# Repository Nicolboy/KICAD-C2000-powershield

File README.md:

# KICAD-C2000-powershield

- **100W / 20V / 5A** — USB-C Power Delivery (STUSB4531QTR) feeds the
  daughter cards in daisy chain, independent from the 11-25V main input
- **5 dedicated LDOs** — isolated 3.3V reference distributed per board
  group instead of one shared regulator, removing a single point of failure
- PCB **routed 100% on 4 layers**, DRC clean

Isolation, power-supply, and interconnect shield for a TMS320 C2000 digital
power-converter controller, supervised by an ESP32-C6 for Wi-Fi, FOTA, and
an OLED status display, designed in KiCad 10.

Shield d'isolation, alimentation et interconnexion pour TMS320 C2000, conçu
sous KiCad 10.

Reprend le projet `shield` de [`KICAD-C2000-devkit`](https://github.com/Nicolboy/KICAD-C2000-devkit)
au moment où son rôle a dépassé le simple support mécanique des deux
devkits : il reçoit désormais le 11-25V externe et produit lui-même les
rails isolés (5V numérique ×2, 3,3V isolation + protection) qu'une carte
de puissance séparée portait jusque-là. D'où le changement de dépôt plutôt
qu'une extension sur place — `KICAD-C2000-devkit` reste inchangé, c'est
l'état précédent, pas un doublon à synchroniser.

Cible : une commande numérique de convertisseur de puissance isolé, pilotée
par un C2000 et supervisée par un ESP32-C6 pour le Wi-Fi, la mise à jour
FOTA et un écran OLED d'état.

---

## Architecture

| Carte | Rôle |
|---|---|
| **Shield** | Alimentation complète (11-25V→5V isolé ×2, 3,3V isolation + protection), **alimentation des cartes filles en USB-C Power Delivery** (STUSB4531QTR, 100W/20V/5A, daisy chain), support mécanique des deux devkits, adaptation de brochage, conditionnement analogique, protections, embase OLED |
| **Cartes DC/DC enfichables** | Une par fonction de puissance, portent chacune l'isolation galvanique qu'elle exige (ou aucune), raccordées au shield par les 4 nappes |
| **Devkit C2000** | MCU, deux LDO 3,3V, JTAG, bouton reset, LED, cavalier de boot |
| **Devkit ESP32** | Wi-Fi, hôte FOTA, écran OLED SPI (`ER-OLEDM032-1B`) |

Liaison shield ↔ cartes DC/DC : six nappes IDC 2 × 10 détrompées (backplane
partagé, decision #17), `3V3_ISO`/`GND` en positions 1/2 puis alternance
signal/masse stricte 1:1 sur les positions suivantes. Deux cartes
(HV, Filament) ont en plus leur propre connecteur dédié (decision #26),
leurs besoins dépassant les réserves du backplane partagé. Écran OLED :
nappe IDC 2 × 8 détrompée dédiée, alimentée avec l'ESP32. Détail complet
dans [`doc/nappes-shield.md`](doc/nappes-shield.md).

---

## Alimentation des cartes filles — USB-C Power Delivery (STUSB4531QTR)

Entrée séparée du 11-25V du shield (decision #23) : un port USB-C négocie
jusqu'à 100W (20V/5A) via un STUSB4531QTR autonome — gestion du contrat PD,
coupure (`VBUS_EN_SNK`) et décharge (`DISCH`/`VBUS_VS_DISCH`) sans eFuse
externe, un seul MOSFET P piloté directement. La puissance négociée est
transmise **en daisy chain** aux cartes filles.

Le STUSB4531 expose son bus de configuration/état (I2C : `STUSB_SCL`/
`STUSB_SDA`, alerte `STUSB_ALERT`) à l'ESP32 via un isolateur dédié
(`ISO1640BD`) — l'ESP32 peut ainsi lire la tension/le courant négociés et
réagir aux alertes sans relier directement le domaine USB-C (`GND_PRI`,
decision #27) au domaine de commande. Cette supervision rejoint son rôle
de superviseur Wi-Fi/FOTA déjà confié ailleurs dans le projet.

Détail et justification dans [`doc/decisions.md`](doc/decisions.md)
(#23, #27).

---

## Le brochage est du code

[`doc/spec-devkit.md`](doc/spec-devkit.md) fait autorité pour le connecteur
devkit — 2 × 28 pour devkit_A (hérité de `KICAD-C2000-devkit`, toujours
valable), **deux embases 2 × 24 à masse en vis-à-vis pour devkit_B**
depuis la decision #25 (`doc/decisions.md`) — les deux devkits ne sont
plus compatibles avec le même shield.
[`doc/nappes-shield.md`](doc/nappes-shield.md) décrit les quatre nappes DC/DC
et l'embase OLED. Contrairement au dépôt d'origine, **il n'y a pas de
générateur ici** — `shield.kicad_sch` est édité à la main dès le départ
(`gen_devkit.py` et consorts restent dans `KICAD-C2000-devkit`, hors sujet
pour ce dépôt).

Les schémas ne contiennent aucun fil : toute la connectivité passe par des
étiquettes globales posées exactement sur la broche concernée — convention
commune à tous les projets KiCad de l'atelier, documentée dans
[`../KICAD.md`](../KICAD.md).

---

## Concevoir avec un agent

Une part du travail est faite par un agent : lecture de datasheet, choix de
boîtier et création d'empreinte custom quand nécessaire (ex.
`lib/NCM3S1205MC.kicad_mod`), traitement par lots, étiquetage. Le placement
des composants et le routage restent manuels.

---

## Reproduire

KiCad 10 requis, `kicad-cli` dans le `PATH`.

```bash
kicad-cli sch erc --exit-code-violations shield.kicad_sch
kicad-cli pcb drc --exit-code-violations shield.kicad_pcb
```

---

## État d'avancement

Travail en cours:

- **Schéma** — dix feuilles (connecteurs devkit/ESP32/OLED, nappes DC/DC,
  alimentation, alimentation USB-C PD des cartes filles, connecteurs dédiés
  carte HV et carte Filament, quatre feuilles de chaînes de protection).
  Toutes les broches réelles portent une empreinte. L'ERC reste à quelques
  centaines de violations, de la même famille que le reste de l'atelier
  (`pin_not_connected`, `isolated_pin_label` sur des réserves non pilotées,
  `endpoint_off_grid`) — pas corrigées d'office, voir `doc/decisions.md`.
- **PCB** — **routé à 100 % sur 4 couches**. `3V3_ISO` distribué sur cinq
  régulateurs dédiés (un par groupe de nappes, décision #29 et suivantes)
  plutôt qu'un LDO unique partagé. DRC propre (quelques dizaines de
  violations résiduelles, catégorisées et justifiées — `lib_footprint_mismatch`
  attendu, `courtyards_overlap` mesuré et accepté). 14 points de test posés
  sur les rails d'alimentation, le bus I2C et la paire de référence ADC,
  étiquetés par nom de net sur `F.Silkscreen`.
- **Connecteur devkit C2000/ESP32, nappes DC/DC, embase OLED** — brochage
  figé, labels vérifiés par ERC contre les coordonnées réelles des broches.

Points encore laissés ouverts (référence exacte de certains connecteurs,
budget de courant détaillé) listés en fin de
[`doc/decisions.md`](doc/decisions.md). Ils attendent une lecture de
datasheet ou une mesure, pas une estimation.

---

## Décisions à ne pas défaire

Trente décisions documentées dans [`doc/decisions.md`](doc/decisions.md),
chacune avec sa raison et ce qui casse si on la défait. Héritées de
`KICAD-C2000-devkit` (#1 à #12) ou propres à ce dépôt (#13 à #30 : migration
de la conversion isolée sur le shield, renumérotation des nappes, embase
OLED et assignation des empreintes, connecteurs dédiés carte HV et carte
Filament, alimentation USB-C Power Delivery des cartes filles, isolation
numérique ESP32 ↔ STUSB4531, suiveur de référence ADC bufferisé).

---

## Licence

[CERN-OHL-S v2](LICENSE) — CERN Open Hardware Licence, fortement réciproque.

Tu peux étudier, modifier, fabriquer et distribuer ce matériel. En
contrepartie, si tu distribues un produit fondé dessus, ou une version
modifiée, tu dois publier les sources correspondantes sous la même licence.

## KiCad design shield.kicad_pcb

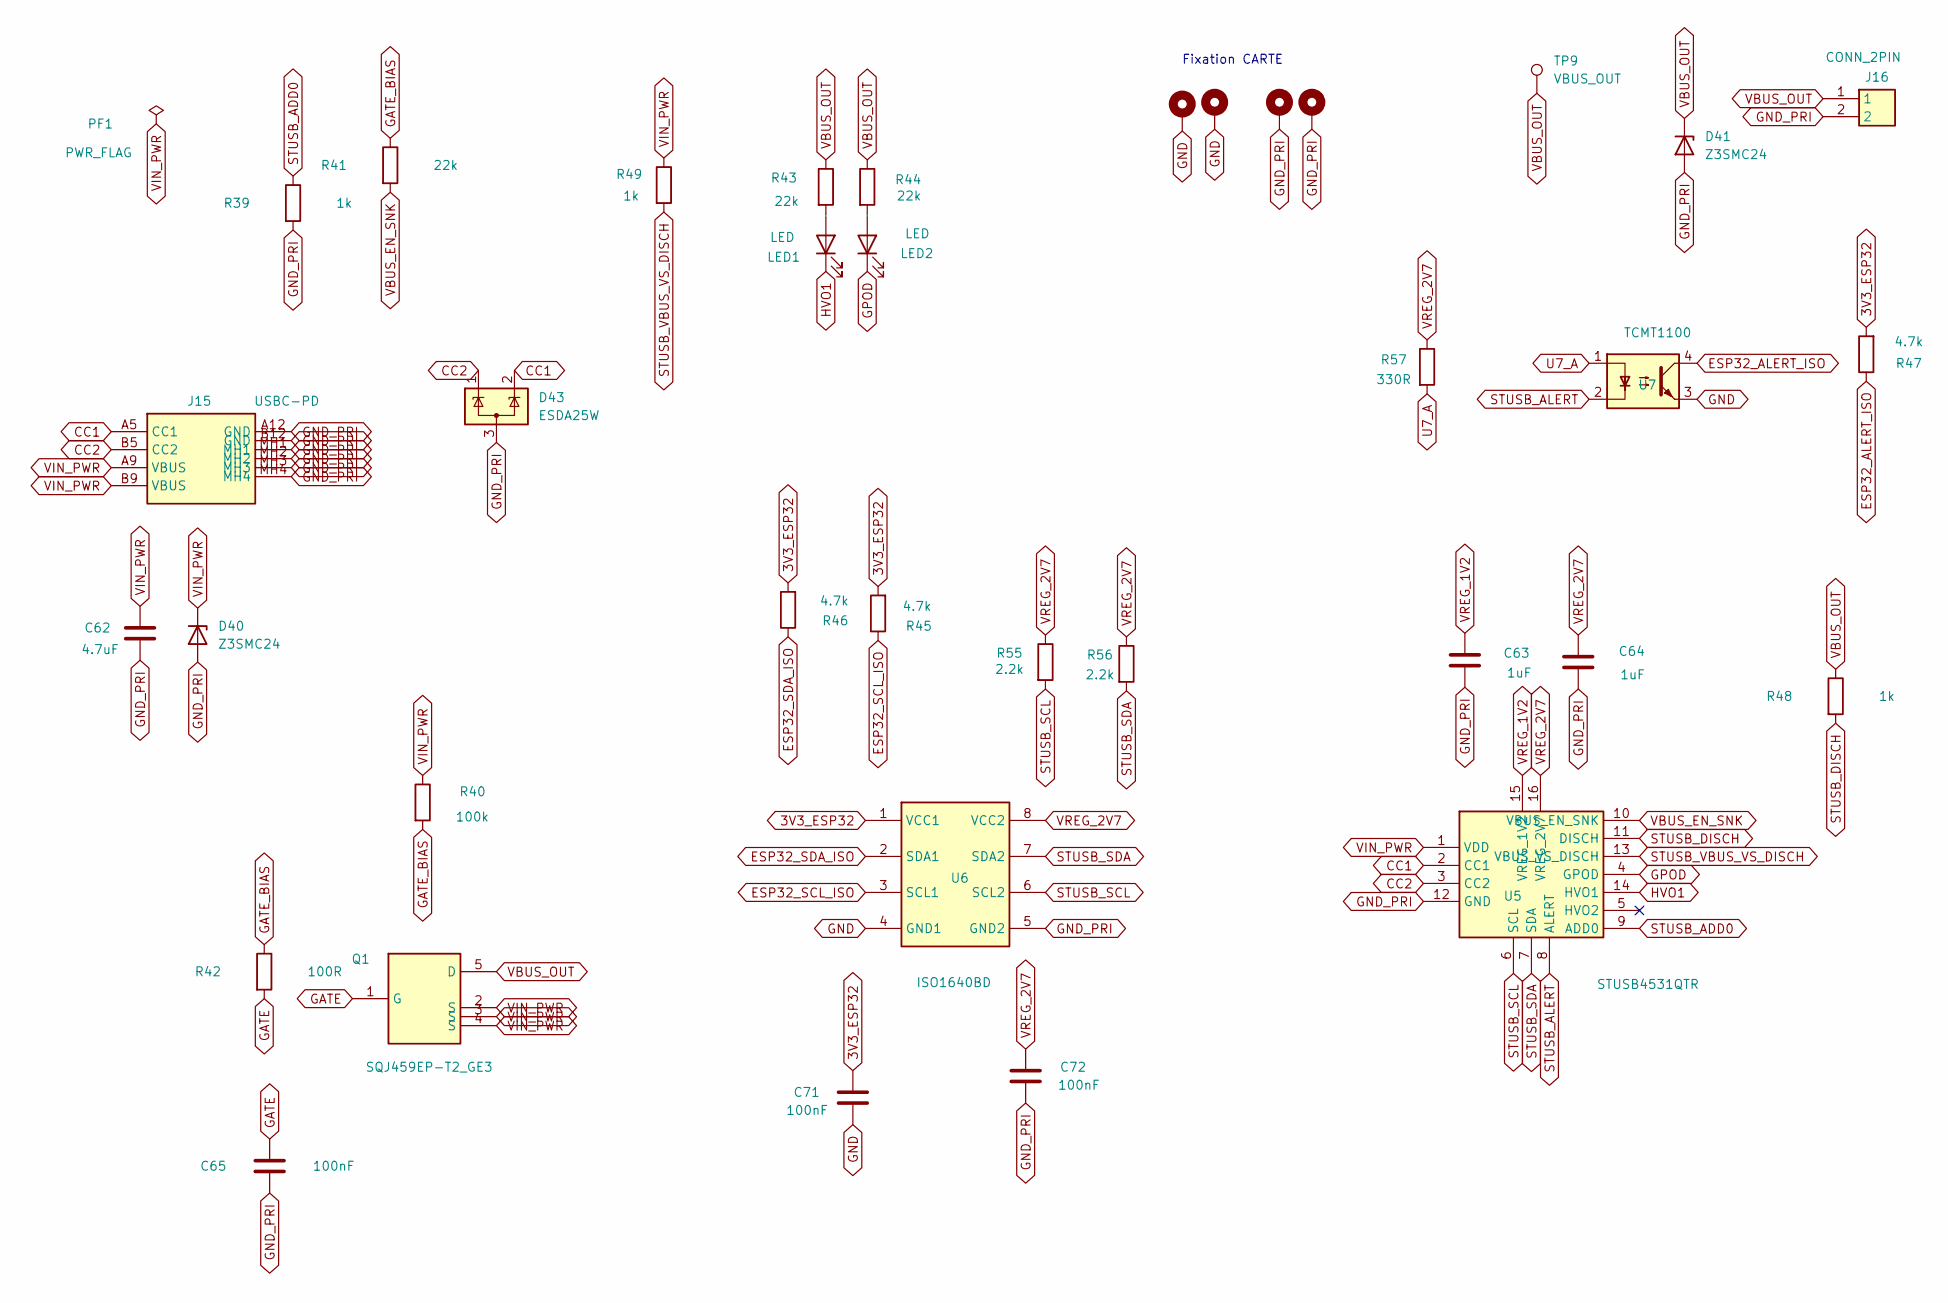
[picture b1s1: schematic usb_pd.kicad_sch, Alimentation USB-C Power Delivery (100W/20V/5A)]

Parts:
C62: 4.7uF; C_0805_2012Metric
C63, C64: 1uF; C_0805_2012Metric
C65, C71, C72: 100nF; C_0805_2012Metric
D40, D41: Z3SMC24; D_SMC
D43: ESDA25W; SOT-23-3
H1, H2, H3, H4: MountingScrew; MountingHole_3.2mm_M3_Pad_Via
J15: USBC-PD; 632722100213
J16: CONN_2PIN; PinSocket_1x02_P2.54mm_Vertical
LED1, LED2: LED; LED_D3.0mm
PF1: PWR_FLAG
Q1: SQJ459EP-T2_GE3; PowerPAK_SO-8_Single
R39, R48, R49: 1k; R_0805_2012Metric
R40: 100k; R_0805_2012Metric
R41, R43, R44: 22k; R_0805_2012Metric
R42: 100R; R_0805_2012Metric
R45, R46, R47: 4.7k; R_0805_2012Metric
R55, R56: 2.2k; R_0805_2012Metric
R57: 330R; R_0805_2012Metric
TP9: VBUS_OUT; TestPoint_Pad_D2.5mm
U5: STUSB4531QTR
U6: ISO1640BD; SOIC-8_3.9x4.9mm_P1.27mm
U7: TCMT1100; SOP-4_4.4x2.6mm_P1.27mm

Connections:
3V3_ESP32: C71.1, R45.2, R46.2, R47.2, U6.1 (VCC1); also elsewhere on the board
CC1: D43.2 (K), J15.A5 (CC1), U5.2 (CC1)
CC2: D43.1 (K), J15.B5 (CC2), U5.3 (CC2)
ESP32_ALERT_ISO: R47.1, U7.4; also elsewhere on the board
ESP32_SCL_ISO: R45.1, U6.3 (SCL1); also elsewhere on the board
ESP32_SDA_ISO: R46.1, U6.2 (SDA1); also elsewhere on the board
GATE: C65.1, Q1.1 (G), R42.2
GATE_BIAS: R40.2, R41.1, R42.1
GND: C71.2, H1.1 (1_1), H2.1 (1_1), U6.4 (GND1), U7.3; also elsewhere on the board
GND_PRI: C62.2, C63.2, C64.2, C65.2, C72.2, D40.2 (A), D41.2 (A), D43.3 (A), H3.1 (1_1), H4.1 (1_1), J15.A12 (GND), J15.B12 (GND), J15.MH1, J15.MH2, J15.MH3, J15.MH4, J16.2, R39.2, U5.12 (GND), U6.5 (GND2); also elsewhere on the board
GPOD: LED2.1 (K), U5.4 (GPOD)
HVO1: LED1.1 (K), U5.14 (HVO1)
unnamed: LED1.2 (A), R43.2
unnamed: LED2.2 (A), R44.2
STUSB_ADD0: R39.1, U5.9 (ADD0)
STUSB_ALERT: U5.8 (ALERT), U7.2
STUSB_DISCH: R48.2, U5.11 (DISCH)
STUSB_SCL: R55.2, U5.6 (SCL), U6.6 (SCL2)
STUSB_SDA: R56.2, U5.7 (SDA), U6.7 (SDA2)
STUSB_VBUS_VS_DISCH: R49.2, U5.13 (VBUS_VS_DISCH)
U7_A: R57.2, U7.1
VBUS_EN_SNK: R41.2, U5.10 (VBUS_EN_SNK)
VBUS_OUT: D41.1 (K), J16.1, Q1.5 (D), R43.1, R44.1, R48.1, TP9.1 (1_1)
VIN_PWR: C62.1, D40.1 (K), J15.A9 (VBUS), J15.B9 (VBUS), PF1.1, Q1.2 (S), Q1.3 (S), Q1.4 (S), R40.1, R49.1, U5.1 (VDD); also elsewhere on the board
VREG_1V2: C63.1, U5.15 (VREG_1V2)
VREG_2V7: C64.1, C72.1, R55.1, R56.1, R57.1, U5.16 (VREG_2V7), U6.8 (VCC2)

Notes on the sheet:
Fixation CARTE

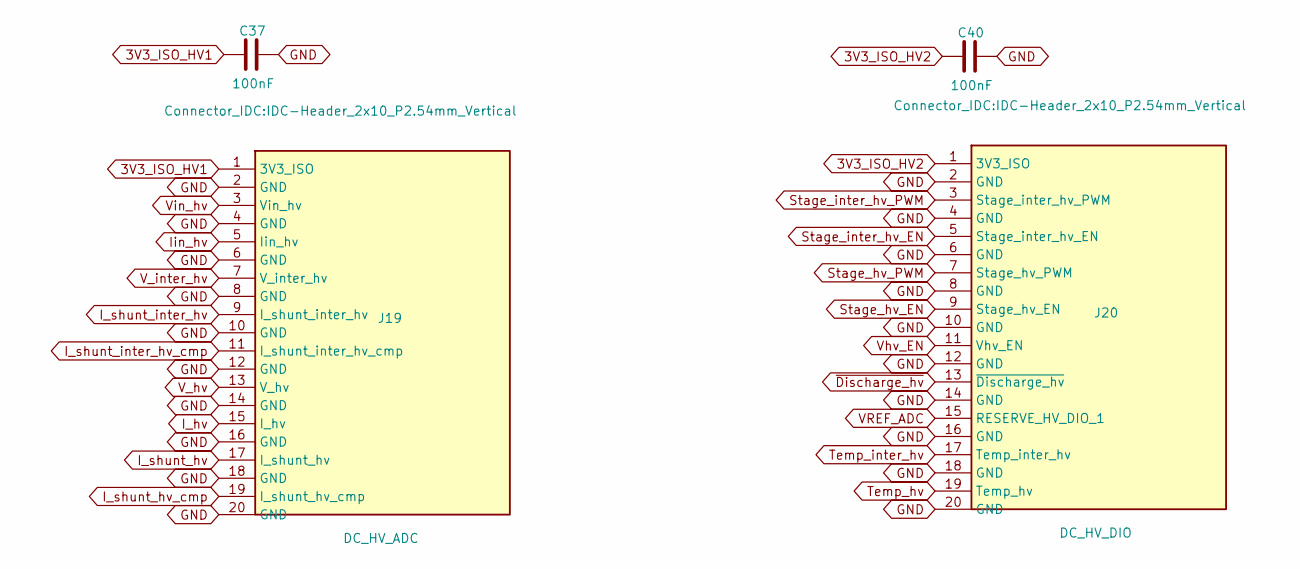
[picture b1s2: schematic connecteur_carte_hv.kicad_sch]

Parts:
C37, C40: 100nF; C_0805_2012Metric
J19: DC_HV_ADC; IDC-Header_2x10_P2.54mm_Vertical
J20: DC_HV_DIO; IDC-Header_2x10_P2.54mm_Vertical

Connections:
3V3_ISO_HV1: C37.1, J19.1 (3V3_ISO); also elsewhere on the board
3V3_ISO_HV2: C40.1, J20.1 (3V3_ISO); also elsewhere on the board
GND: C37.2, C40.2, J19.2 (GND), J19.4 (GND), J19.6 (GND), J19.8 (GND), J19.10 (GND), J19.12 (GND), J19.14 (GND), J19.16 (GND), J19.18 (GND), J19.20 (GND), J20.2 (GND), J20.4 (GND), J20.6 (GND), J20.8 (GND), J20.10 (GND), J20.12 (GND), J20.14 (GND), J20.16 (GND), J20.18 (GND), J20.20 (GND); also elsewhere on the board
I_hv: J19.15 (I_hv); also elsewhere on the board
I_shunt_hv: J19.17 (I_shunt_hv); also elsewhere on the board
I_shunt_hv_cmp: J19.19 (I_shunt_hv_cmp); also elsewhere on the board
I_shunt_inter_hv: J19.9 (I_shunt_inter_hv); also elsewhere on the board
I_shunt_inter_hv_cmp: J19.11 (I_shunt_inter_hv_cmp); also elsewhere on the board
Iin_hv: J19.5 (Iin_hv); also elsewhere on the board
Stage_hv_EN: J20.9 (Stage_hv_EN); also elsewhere on the board
Stage_hv_PWM: J20.7 (Stage_hv_PWM); also elsewhere on the board
Stage_inter_hv_EN: J20.5 (Stage_inter_hv_EN); also elsewhere on the board
Stage_inter_hv_PWM: J20.3 (Stage_inter_hv_PWM); also elsewhere on the board
Temp_hv: J20.19 (Temp_hv); also elsewhere on the board
Temp_inter_hv: J20.17 (Temp_inter_hv); also elsewhere on the board
VREF_ADC: J20.15 (RESERVE_HV_DIO_1); also elsewhere on the board
V_hv: J19.13 (V_hv); also elsewhere on the board
V_inter_hv: J19.7 (V_inter_hv); also elsewhere on the board
Vhv_EN: J20.11 (Vhv_EN); also elsewhere on the board
Vin_hv: J19.3 (Vin_hv); also elsewhere on the board
~Discharge_hv: J20.13 (~Discharge_hv); also elsewhere on the board

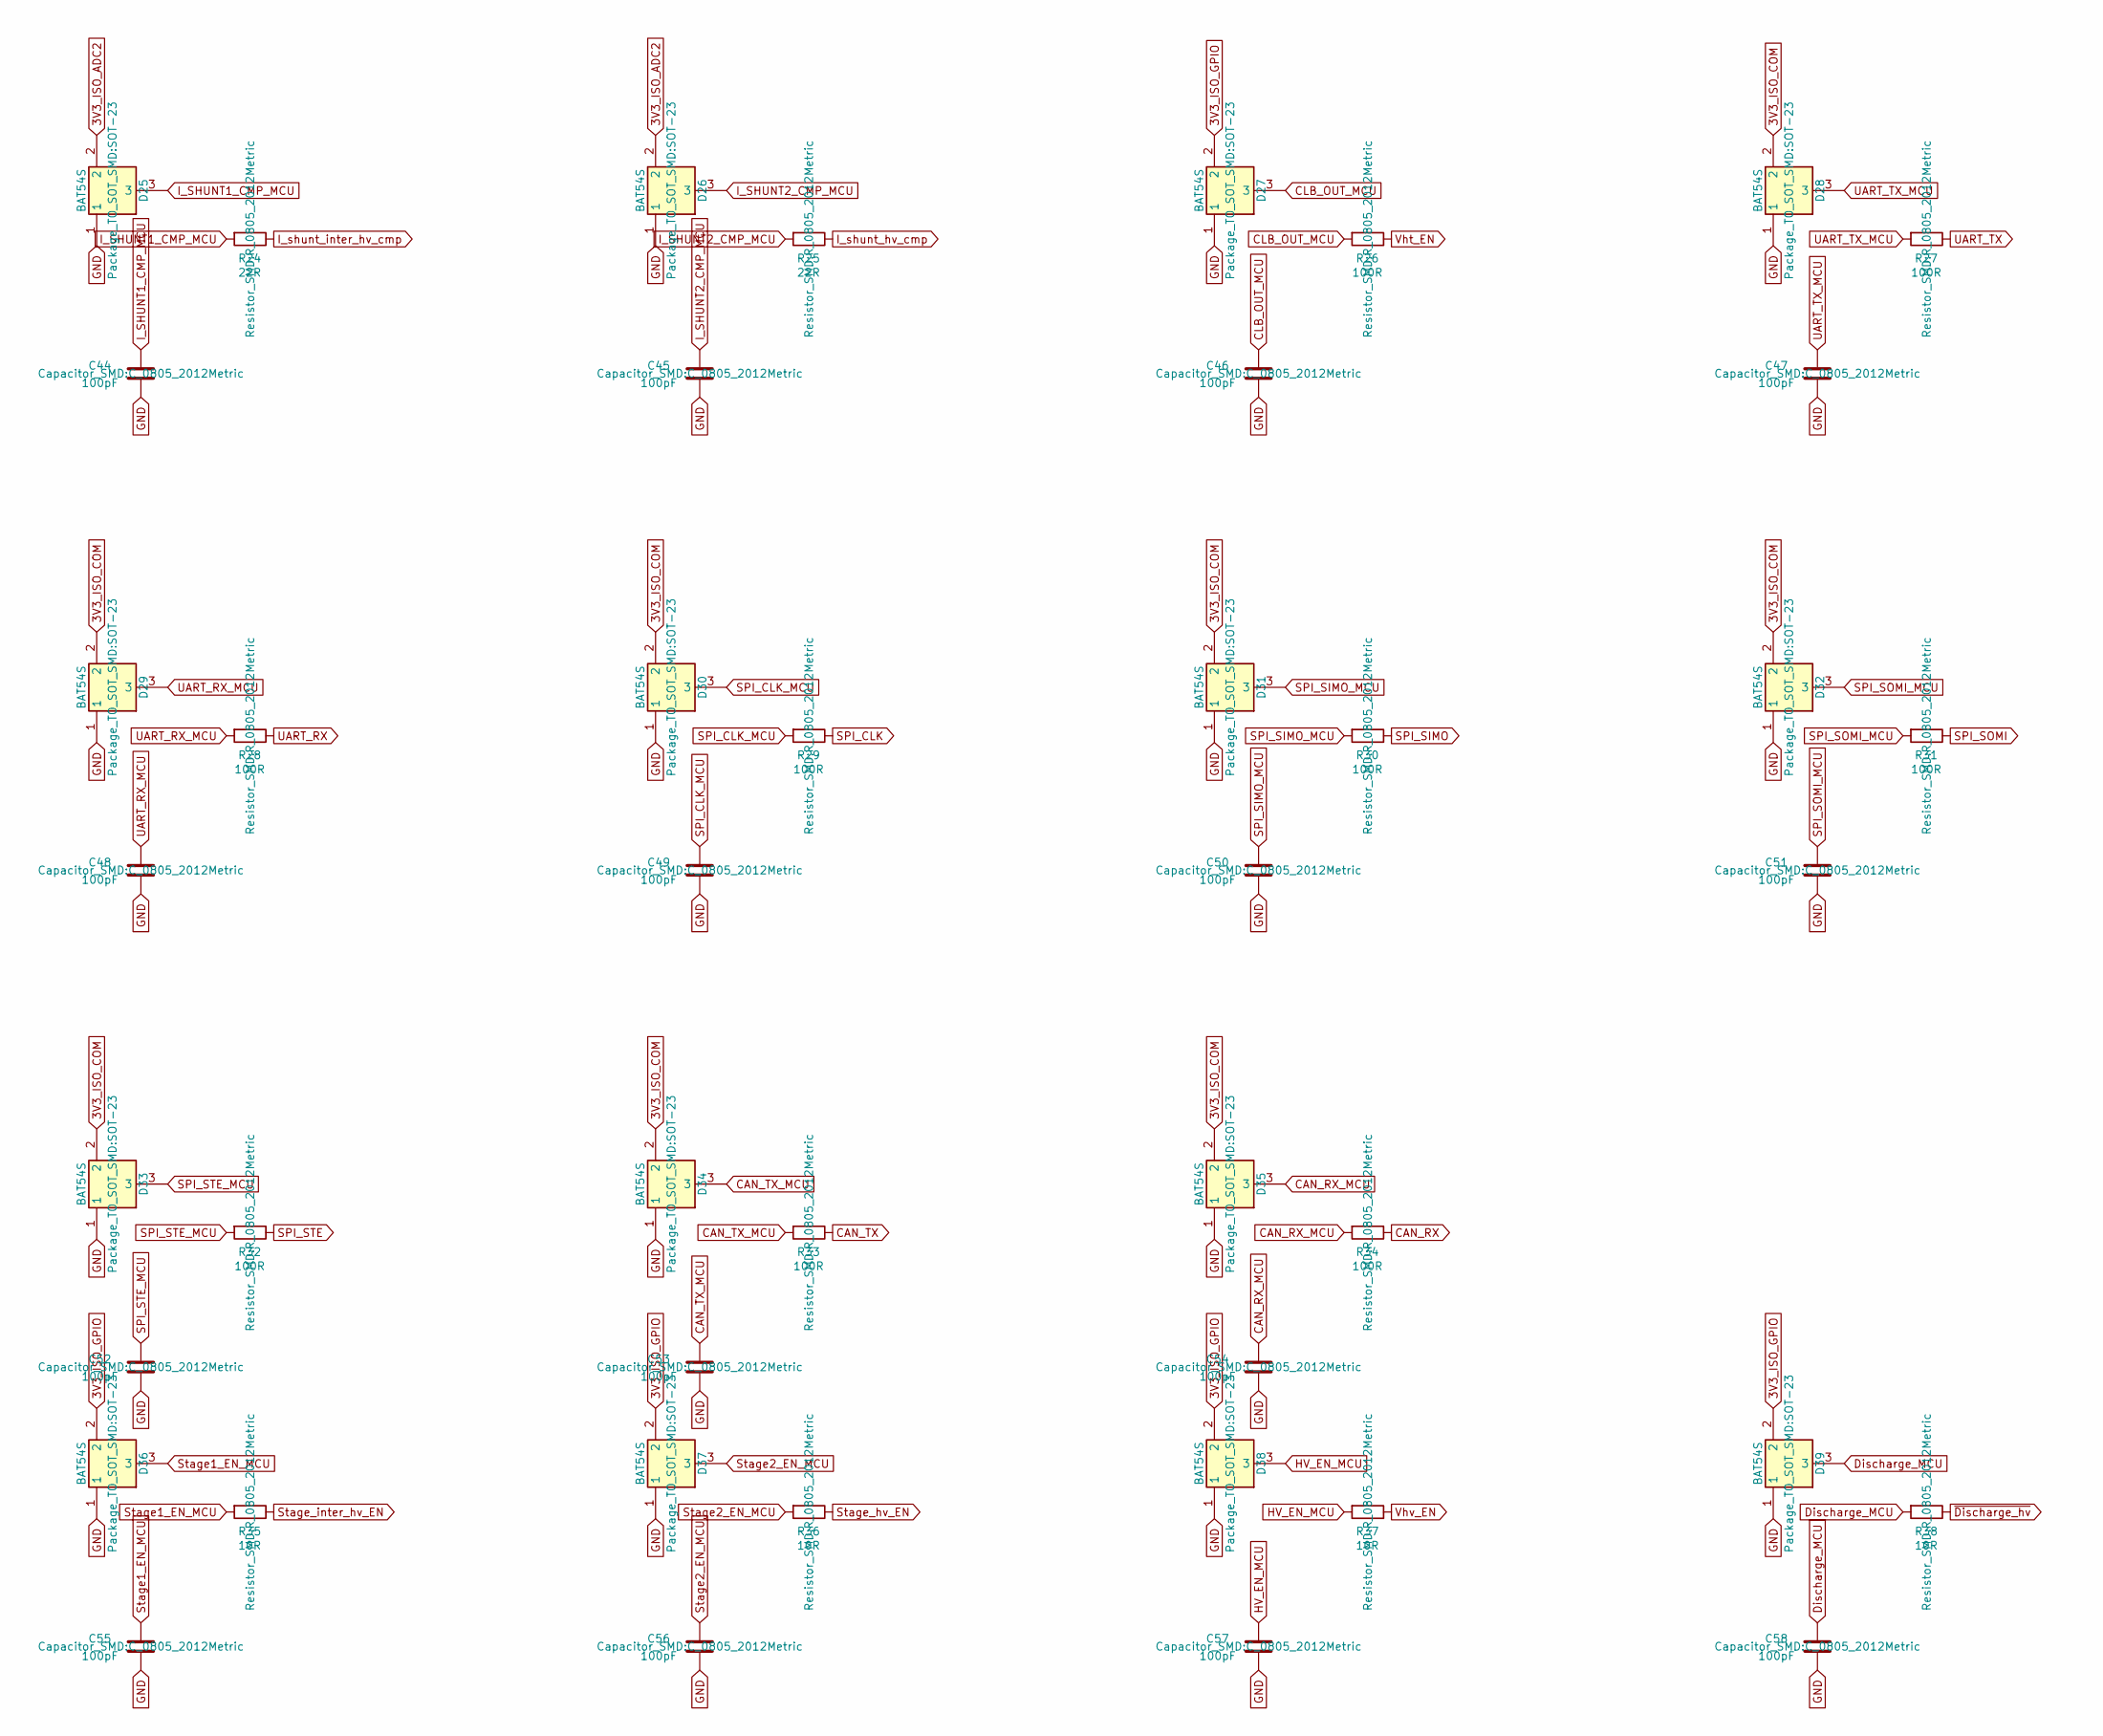
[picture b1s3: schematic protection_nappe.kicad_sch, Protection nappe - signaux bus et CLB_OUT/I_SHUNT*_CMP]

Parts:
C44, C45, C46, C47, C48, C49, C50, C51, C52, C53, C54, C55, C56, C57, C58: 100pF; C_0805_2012Metric
D25, D26, D27, D28, D29, D30, D31, D32, D33, D34, D35, D36, D37, D38, D39: BAT54S; SOT-23
R24, R25: 22R; R_0805_2012Metric
R26, R27, R28, R29, R30, R31, R32, R33, R34: 100R; R_0805_2012Metric
R35, R36, R37, R38: 10R; R_0805_2012Metric

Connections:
3V3_ISO_ADC2: D25.2, D26.2; also elsewhere on the board
3V3_ISO_COM: D28.2, D29.2, D30.2, D31.2, D32.2, D33.2, D34.2, D35.2; also elsewhere on the board
3V3_ISO_GPIO: D27.2, D36.2, D37.2, D38.2, D39.2; also elsewhere on the board
CAN_RX: R34.1; also elsewhere on the board
CAN_RX_MCU: C54.2, D35.3, R34.2; also elsewhere on the board
CAN_TX: R33.1; also elsewhere on the board
CAN_TX_MCU: C53.2, D34.3, R33.2; also elsewhere on the board
CLB_OUT_MCU: C46.2, D27.3, R26.2; also elsewhere on the board
Discharge_MCU: C58.2, D39.3, R38.2; also elsewhere on the board
GND: C44.1, C45.1, C46.1, C47.1, C48.1, C49.1, C50.1, C51.1, C52.1, C53.1, C54.1, C55.1, C56.1, C57.1, C58.1, D25.1, D26.1, D27.1, D28.1, D29.1, D30.1, D31.1, D32.1, D33.1, D34.1, D35.1, D36.1, D37.1, D38.1, D39.1; also elsewhere on the board
HV_EN_MCU: C57.2, D38.3, R37.2; also elsewhere on the board
I_SHUNT1_CMP_MCU: C44.2, D25.3, R24.2; also elsewhere on the board
I_SHUNT2_CMP_MCU: C45.2, D26.3, R25.2; also elsewhere on the board
I_shunt_hv_cmp: R25.1; also elsewhere on the board
I_shunt_inter_hv_cmp: R24.1; also elsewhere on the board
SPI_CLK: R29.1; also elsewhere on the board
SPI_CLK_MCU: C49.2, D30.3, R29.2; also elsewhere on the board
SPI_SIMO: R30.1; also elsewhere on the board
SPI_SIMO_MCU: C50.2, D31.3, R30.2; also elsewhere on the board
SPI_SOMI: R31.1; also elsewhere on the board
SPI_SOMI_MCU: C51.2, D32.3, R31.2; also elsewhere on the board
SPI_STE: R32.1; also elsewhere on the board
SPI_STE_MCU: C52.2, D33.3, R32.2; also elsewhere on the board
Stage1_EN_MCU: C55.2, D36.3, R35.2; also elsewhere on the board
Stage2_EN_MCU: C56.2, D37.3, R36.2; also elsewhere on the board
Stage_hv_EN: R36.1; also elsewhere on the board
Stage_inter_hv_EN: R35.1; also elsewhere on the board
UART_RX: R28.1; also elsewhere on the board
UART_RX_MCU: C48.2, D29.3, R28.2; also elsewhere on the board
UART_TX: R27.1; also elsewhere on the board
UART_TX_MCU: C47.2, D28.3, R27.2; also elsewhere on the board
Vht_EN: R26.1; also elsewhere on the board
Vhv_EN: R37.1; also elsewhere on the board
~Discharge_hv: R38.1; also elsewhere on the board

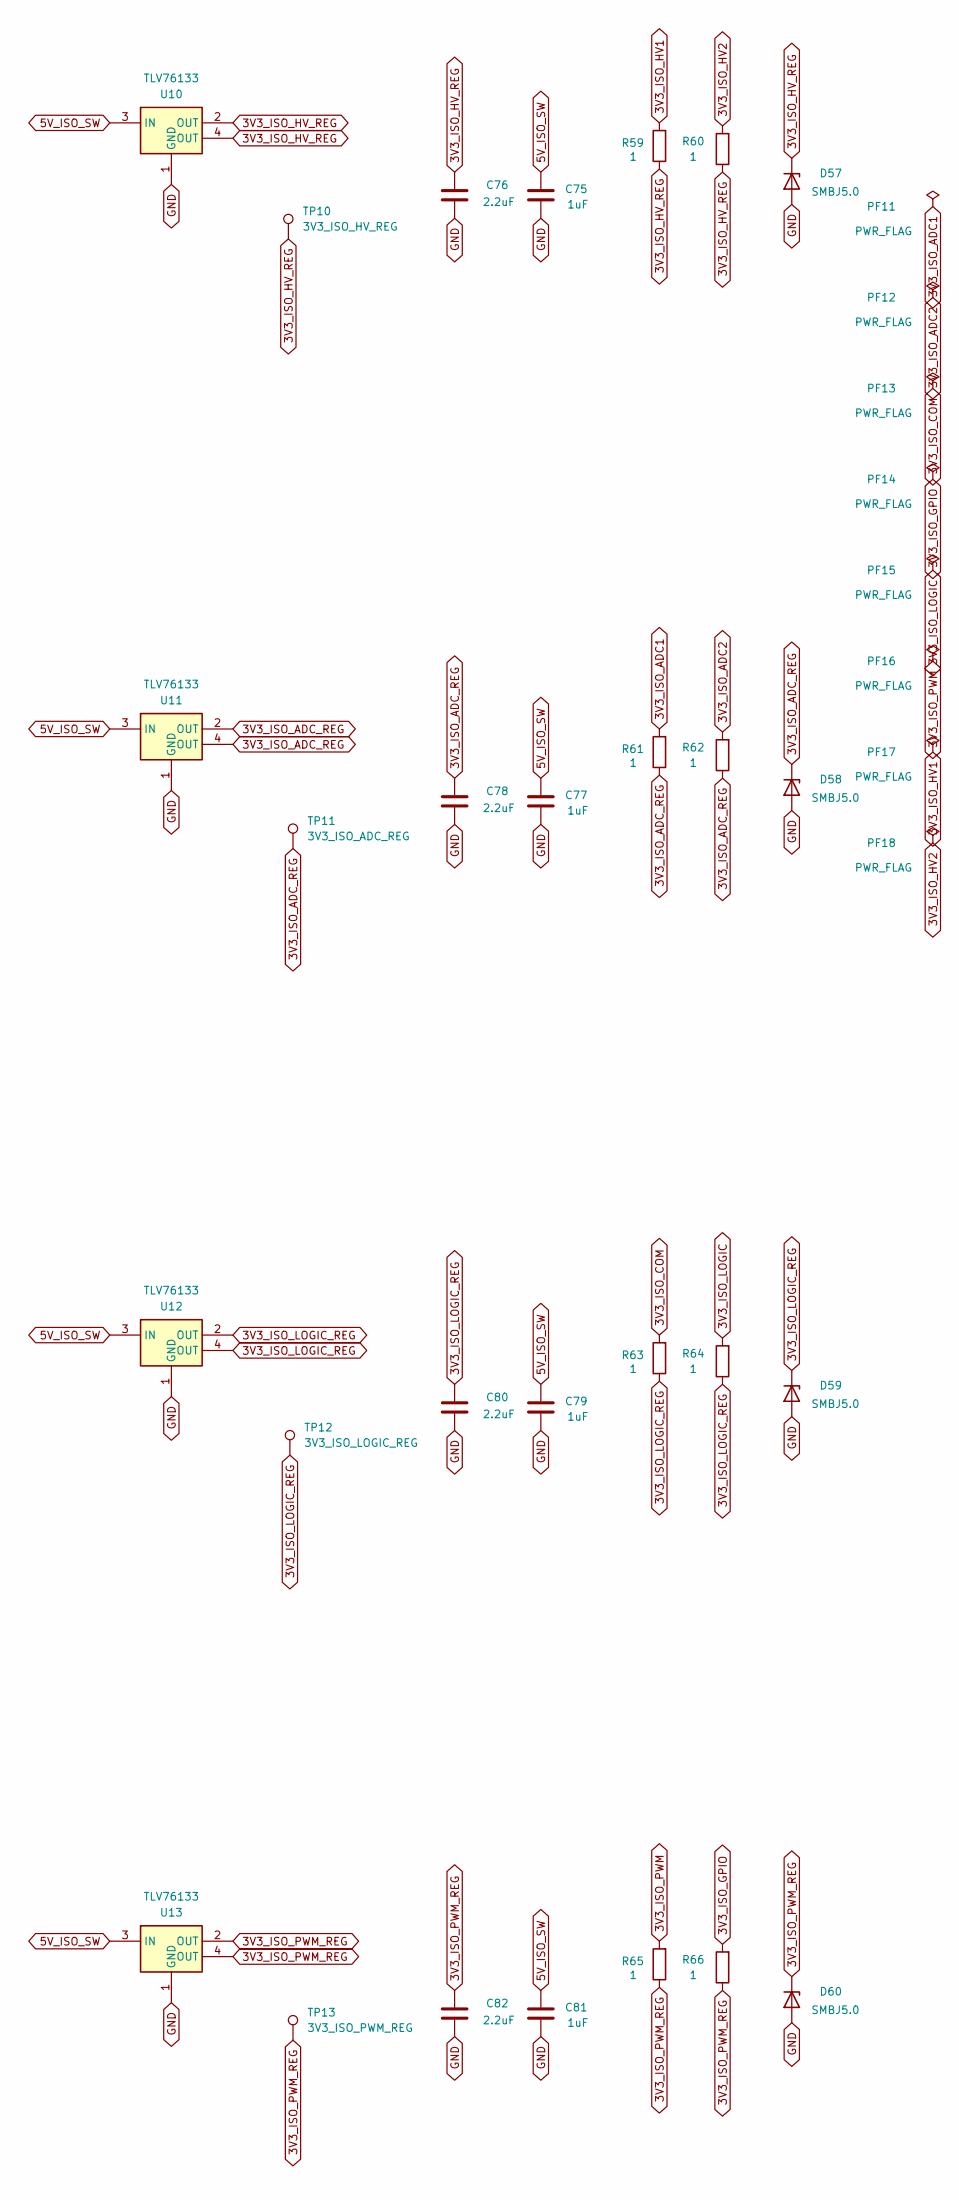
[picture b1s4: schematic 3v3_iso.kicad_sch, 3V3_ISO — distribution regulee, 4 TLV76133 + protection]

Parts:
C75, C77, C79, C81: 1uF; C_0805_2012Metric
C76, C78, C80, C82: 2.2uF; C_0805_2012Metric
D57, D58, D59, D60: SMBJ5.0; D_SMB
PF11, PF12, PF13, PF14, PF15, PF16, PF17, PF18: PWR_FLAG
R59, R60, R61, R62, R63, R64, R65, R66: 1; R_0805_2012Metric
TP10: 3V3_ISO_HV_REG; TestPoint_Pad_D2.5mm
TP11: 3V3_ISO_ADC_REG; TestPoint_Pad_D2.5mm
TP12: 3V3_ISO_LOGIC_REG; TestPoint_Pad_D2.5mm
TP13: 3V3_ISO_PWM_REG; TestPoint_Pad_D2.5mm
U10, U11, U12, U13: TLV76133; SOT-223

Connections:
3V3_ISO_ADC1: PF11.1, R61.2; also elsewhere on the board
3V3_ISO_ADC2: PF12.1, R62.2; also elsewhere on the board
3V3_ISO_ADC_REG: C78.1, D58.1 (K), R61.1, R62.1, TP11.1 (1_1), U11.2 (OUT), U11.4 (OUT)
3V3_ISO_COM: PF13.1, R63.2; also elsewhere on the board
3V3_ISO_GPIO: PF14.1, R66.2; also elsewhere on the board
3V3_ISO_HV1: PF17.1, R59.2; also elsewhere on the board
3V3_ISO_HV2: PF18.1, R60.2; also elsewhere on the board
3V3_ISO_HV_REG: C76.1, D57.1 (K), R59.1, R60.1, TP10.1 (1_1), U10.2 (OUT), U10.4 (OUT)
3V3_ISO_LOGIC: PF15.1, R64.2; also elsewhere on the board
3V3_ISO_LOGIC_REG: C80.1, D59.1 (K), R63.1, R64.1, TP12.1 (1_1), U12.2 (OUT), U12.4 (OUT)
3V3_ISO_PWM: PF16.1, R65.2; also elsewhere on the board
3V3_ISO_PWM_REG: C82.1, D60.1 (K), R65.1, R66.1, TP13.1 (1_1), U13.2 (OUT), U13.4 (OUT)
5V_ISO_SW: C75.1, C77.1, C79.1, C81.1, U10.3 (IN), U11.3 (IN), U12.3 (IN), U13.3 (IN); also elsewhere on the board
GND: C75.2, C76.2, C77.2, C78.2, C79.2, C80.2, C81.2, C82.2, D57.2 (A), D58.2 (A), D59.2 (A), D60.2 (A), U10.1 (GND), U11.1 (GND), U12.1 (GND), U13.1 (GND); also elsewhere on the board

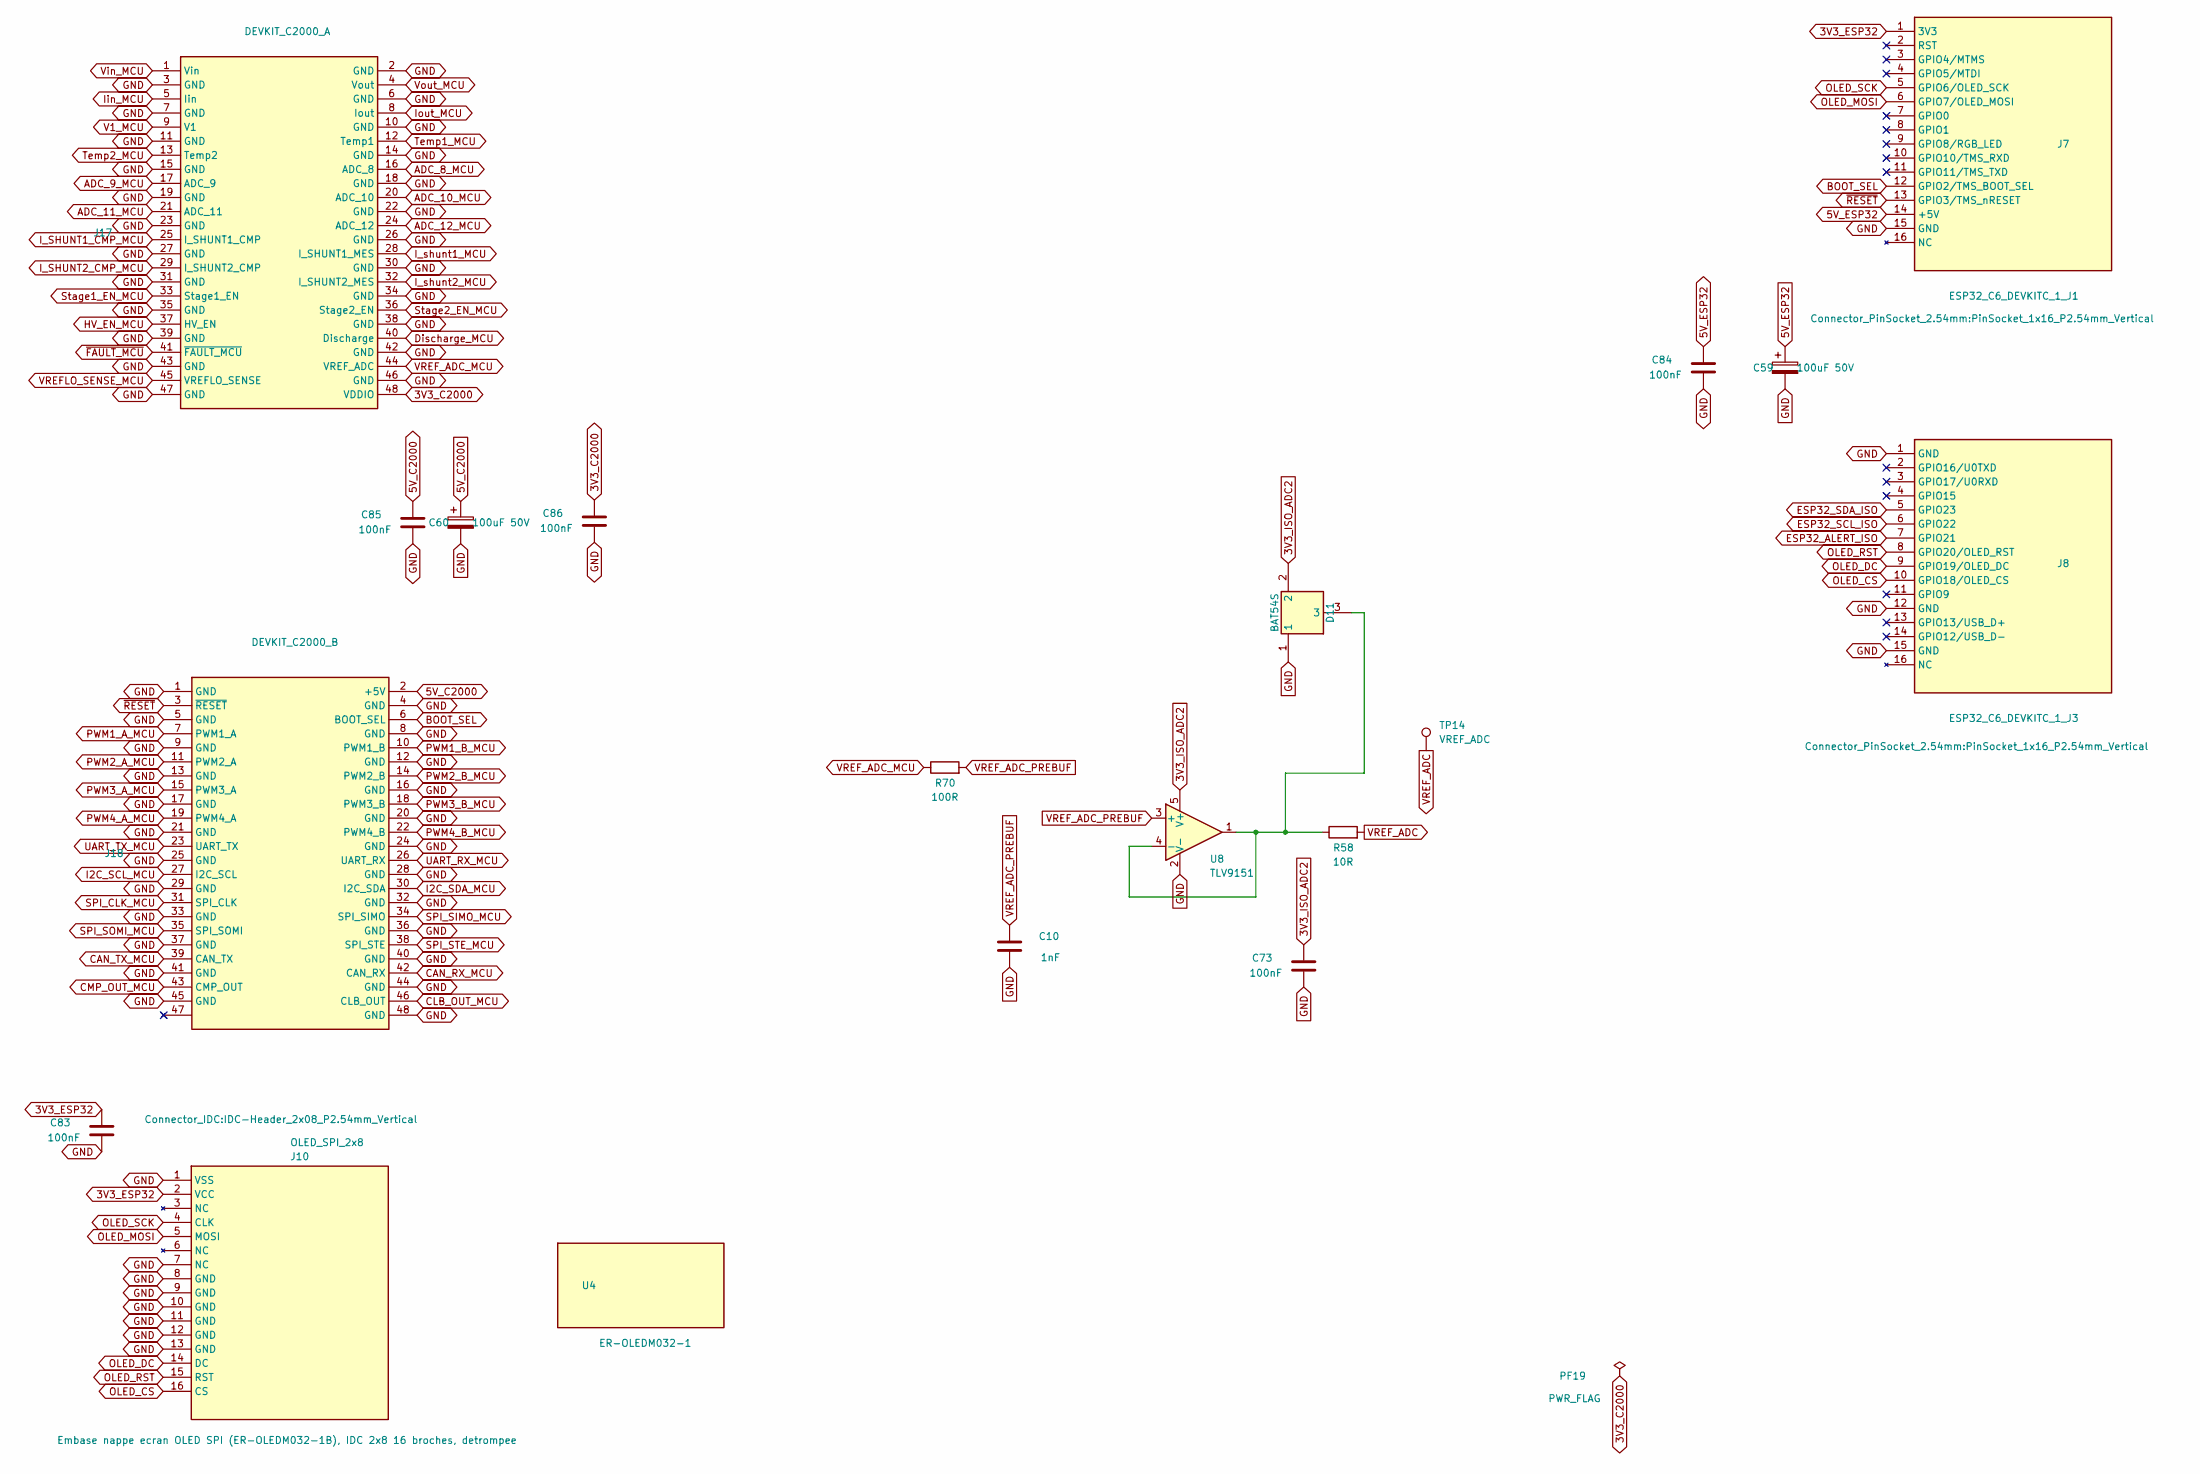
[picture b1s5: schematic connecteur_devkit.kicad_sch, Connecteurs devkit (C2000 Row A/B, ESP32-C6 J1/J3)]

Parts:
C10: 1nF; C_0805_2012Metric
C59, C60: 100uF 50V; CP_Elec_8x10.5
C73, C83, C84, C85, C86: 100nF; C_0805_2012Metric
D11: BAT54S; SOT-23
J7: ESP32_C6_DEVKITC_1_J1; PinSocket_1x16_P2.54mm_Vertical
J8: ESP32_C6_DEVKITC_1_J3; PinSocket_1x16_P2.54mm_Vertical
J10: OLED_SPI_2x8; IDC-Header_2x08_P2.54mm_Vertical
J17: DEVKIT_C2000_A; PinSocket_2x24_P2.54mm_Vertical
J18: DEVKIT_C2000_B; PinSocket_2x24_P2.54mm_Vertical
PF19: PWR_FLAG
R58: 10R; R_0805_2012Metric
R70: 100R; R_0805_2012Metric
TP14: VREF_ADC; TestPoint_Pad_D2.5mm
U4: ER-OLEDM032-1
U8: TLV9151; SOT-23-5

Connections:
3V3_C2000: C86.2, J17.48 (VDDIO), PF19.1; also elsewhere on the board
3V3_ESP32: C83.2, J7.1 (3V3), J10.2 (VCC); also elsewhere on the board
3V3_ISO_ADC2: C73.2, D11.2, U8.5 (V+); also elsewhere on the board
5V_C2000: C60.1, C85.2, J18.2 (+5V); also elsewhere on the board
5V_ESP32: C59.1, C84.2, J7.14 (+5V); also elsewhere on the board
ADC_8_MCU: J17.16 (ADC_8); also elsewhere on the board
ADC_9_MCU: J17.17 (ADC_9); also elsewhere on the board
ADC_10_MCU: J17.20 (ADC_10); also elsewhere on the board
ADC_11_MCU: J17.21 (ADC_11); also elsewhere on the board
ADC_12_MCU: J17.24 (ADC_12); also elsewhere on the board
BOOT_SEL: J7.12 (GPIO2/TMS_BOOT_SEL), J18.6 (BOOT_SEL)
CAN_RX_MCU: J18.42 (CAN_RX); also elsewhere on the board
CAN_TX_MCU: J18.39 (CAN_TX); also elsewhere on the board
CLB_OUT_MCU: J18.46 (CLB_OUT); also elsewhere on the board
CMP_OUT_MCU: J18.43 (CMP_OUT); also elsewhere on the board
Discharge_MCU: J17.40 (Discharge); also elsewhere on the board
ESP32_ALERT_ISO: J8.7 (GPIO21); also elsewhere on the board
ESP32_SCL_ISO: J8.6 (GPIO22); also elsewhere on the board
ESP32_SDA_ISO: J8.5 (GPIO23); also elsewhere on the board
GND: C10.1, C59.2, C60.2, C73.1, C83.1, C84.1, C85.1, C86.1, D11.1, J7.15 (GND), J8.1 (GND), J8.12 (GND), J8.15 (GND), J10.1 (VSS), J10.7 (NC), J10.8 (GND), J10.9 (GND), J10.10 (GND), J10.11 (GND), J10.12 (GND), J10.13 (GND), J17.2 (GND), J17.3 (GND), J17.6 (GND), J17.7 (GND), J17.10 (GND), J17.11 (GND), J17.14 (GND), J17.15 (GND), J17.18 (GND), J17.19 (GND), J17.22 (GND), J17.23 (GND), J17.26 (GND), J17.27 (GND), J17.30 (GND), J17.31 (GND), J17.34 (GND), J17.35 (GND), J17.38 (GND), J17.39 (GND), J17.42 (GND), J17.43 (GND), J17.46 (GND), J17.47 (GND), J18.1 (GND), J18.4 (GND), J18.5 (GND), J18.8 (GND), J18.9 (GND), J18.12 (GND), J18.13 (GND), J18.16 (GND), J18.17 (GND), J18.20 (GND), J18.21 (GND), J18.24 (GND), J18.25 (GND), J18.28 (GND), J18.29 (GND), J18.32 (GND), J18.33 (GND), J18.36 (GND), J18.37 (GND), J18.40 (GND), J18.41 (GND), J18.44 (GND), J18.45 (GND), J18.48 (GND), U8.2 (V-); also elsewhere on the board
HV_EN_MCU: J17.37 (HV_EN); also elsewhere on the board
I2C_SCL_MCU: J18.27 (I2C_SCL); also elsewhere on the board
I2C_SDA_MCU: J18.30 (I2C_SDA); also elsewhere on the board
I_SHUNT1_CMP_MCU: J17.25 (I_SHUNT1_CMP); also elsewhere on the board
I_SHUNT2_CMP_MCU: J17.29 (I_SHUNT2_CMP); also elsewhere on the board
I_shunt1_MCU: J17.28 (I_SHUNT1_MES); also elsewhere on the board
I_shunt2_MCU: J17.32 (I_SHUNT2_MES); also elsewhere on the board
Iin_MCU: J17.5 (Iin); also elsewhere on the board
Iout_MCU: J17.8 (Iout); also elsewhere on the board
unnamed: D11.3, R58.1, U8.1, U8.4 (-)
OLED_CS: J8.10 (GPIO18/OLED_CS), J10.16 (CS)
OLED_DC: J8.9 (GPIO19/OLED_DC), J10.14 (DC)
OLED_MOSI: J7.6 (GPIO7/OLED_MOSI), J10.5 (MOSI)
OLED_RST: J8.8 (GPIO20/OLED_RST), J10.15 (RST)
OLED_SCK: J7.5 (GPIO6/OLED_SCK), J10.4 (CLK)
PWM1_A_MCU: J18.7 (PWM1_A); also elsewhere on the board
PWM1_B_MCU: J18.10 (PWM1_B); also elsewhere on the board
PWM2_A_MCU: J18.11 (PWM2_A); also elsewhere on the board
PWM2_B_MCU: J18.14 (PWM2_B); also elsewhere on the board
PWM3_A_MCU: J18.15 (PWM3_A); also elsewhere on the board
PWM3_B_MCU: J18.18 (PWM3_B); also elsewhere on the board
PWM4_A_MCU: J18.19 (PWM4_A); also elsewhere on the board
PWM4_B_MCU: J18.22 (PWM4_B); also elsewhere on the board
SPI_CLK_MCU: J18.31 (SPI_CLK); also elsewhere on the board
SPI_SIMO_MCU: J18.34 (SPI_SIMO); also elsewhere on the board
SPI_SOMI_MCU: J18.35 (SPI_SOMI); also elsewhere on the board
SPI_STE_MCU: J18.38 (SPI_STE); also elsewhere on the board
Stage1_EN_MCU: J17.33 (Stage1_EN); also elsewhere on the board
Stage2_EN_MCU: J17.36 (Stage2_EN); also elsewhere on the board
Temp1_MCU: J17.12 (Temp1); also elsewhere on the board
Temp2_MCU: J17.13 (Temp2); also elsewhere on the board
UART_RX_MCU: J18.26 (UART_RX); also elsewhere on the board
UART_TX_MCU: J18.23 (UART_TX); also elsewhere on the board
V1_MCU: J17.9 (V1); also elsewhere on the board
VREFLO_SENSE_MCU: J17.45 (VREFLO_SENSE); also elsewhere on the board
VREF_ADC: R58.2, TP14.1 (1_1); also elsewhere on the board
VREF_ADC_MCU: J17.44 (VREF_ADC), R70.1
VREF_ADC_PREBUF: C10.2, R70.2, U8.3 (+)
Vin_MCU: J17.1 (Vin); also elsewhere on the board
Vout_MCU: J17.4 (Vout); also elsewhere on the board
~FAULT_MCU: J17.41 (~FAULT_MCU); also elsewhere on the board
~RESET: J7.13 (GPIO3/TMS_nRESET), J18.3 (~RESET)
